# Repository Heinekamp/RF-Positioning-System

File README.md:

# RF-Positioning-System

A cost-effective 2-axis RF positioning system for characterizing antenna directionality in azimuth and elevation, developed as a bachelor project at the EMES chair at the University of Freiburg. Both axes rotate independently around a fixed centre of rotation, controlled by an ESP32 over a standard [SCPI](https://en.wikipedia.org/wiki/Standard_Commands_for_Programmable_Instruments) interface over Ethernet or USB.

## Key Specifications

| Parameter | Value |
|---|---|
| Positioning range | 360° independent rotation, azimuth and elevation |
| Positioning accuracy | 1.0° |
| Positioning speed | 0.1°/s – 180°/s |
| Frequency range | 600 MHz – 6 GHz |
| Payload | 500 g |
| DUT height above base | 1.0 m |
| Base footprint | 40 cm × 40 cm |
| Total weight | ~20 kg |
| Communication | USB, Ethernet (SCPI) |
| Power supply | 12 V DC |

## Measured Performance

Repeatability of both rotation axes, measured with a motion-capture system across 10 repeated full revolutions:

<table>
<tr>
<td width="50%"></td>
<td width="50%"></td>
</tr>
<tr>
<td><sub>Azimuth positioning deviation from the commanded angle, measured after each of 10 repeated full revolutions.</sub></td>
<td><sub>Elevation positioning deviation from the commanded angle, measured the same way.</sub></td>
</tr>
</table>

Radiated emissions of the fully assembled, enclosed system were measured with the Ethernet link forced to 10&nbsp;Mbit/s, against 20 dB under the CISPR 11 Class B radiated emissions limit:

<table>
<tr>
<td width="50%"></td>
<td width="50%"></td>
</tr>
<tr>
<td><sub>Radiated field strength from 0.5–4.5 GHz, vertical and horizontal antenna polarization, against the CISPR 11 Class B limit.</sub></td>
<td><sub>Detail view of the 0.6–1.0 GHz band from the same measurement — individual emission peaks all remain more than 20 dB below the compliance limit shown at left.</sub></td>
</tr>
</table>

## Hardware

The controller is a custom PCB (KiCad project in [`Electrical/Controller`](Electrical/Controller)) built around an ESP32, driving two TMC2209 stepper drivers over UART. The mechanical design was done in Autodesk Fusion 360; the full CAD model is available in the [Fusion 360 online viewer](https://a360.co/42XAUax).

## Software

The firmware is written in C++ using the Arduino framework in PlatformIO (see [`Code/RF-Positioning-System`](Code/RF-Positioning-System)), and exposes a standards-compliant SCPI command set over Ethernet and USB — see that folder's [readme](Code/RF-Positioning-System/readme.md) for the full command reference and a quick-start example.

Firmware documentation is generated with Doxygen and published [here](https://heinekamp.github.io/RF-Positioning-System/index.html). If the following badge is green, it's up to date: .

## Documentation

The [Service Manual](Documentation/manual/ServiceManual.pdf) covers the system's theory of operation, the full SCPI interface, and maintenance/component-replacement procedures.

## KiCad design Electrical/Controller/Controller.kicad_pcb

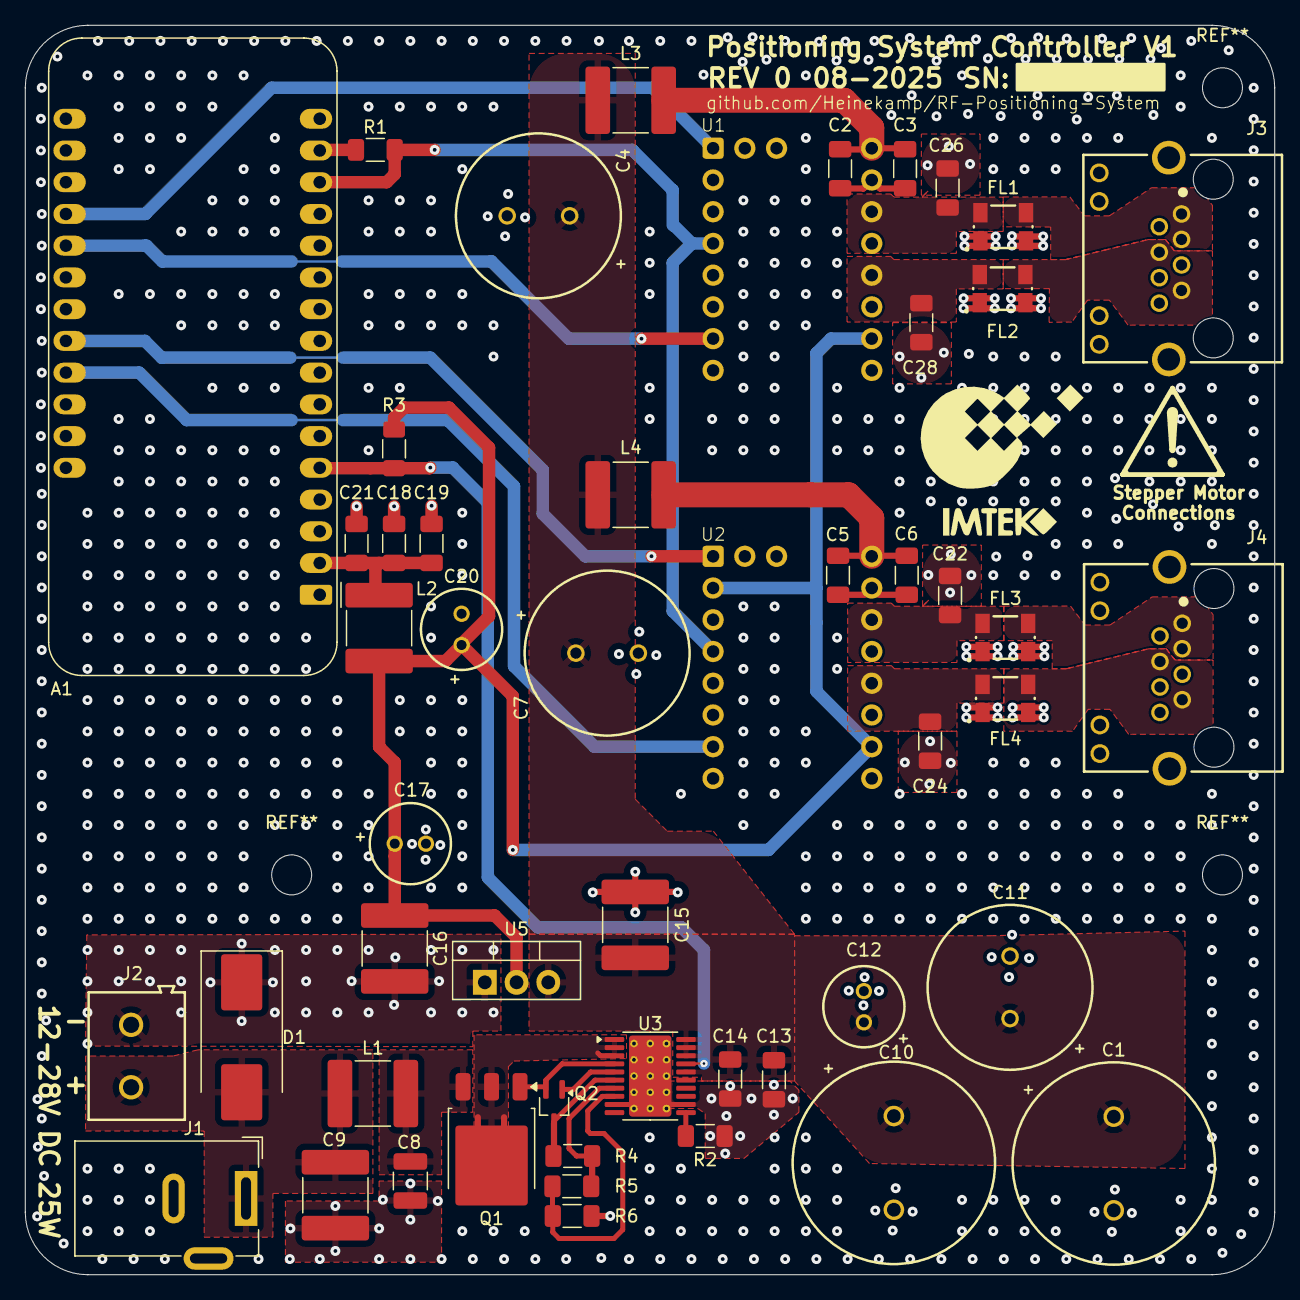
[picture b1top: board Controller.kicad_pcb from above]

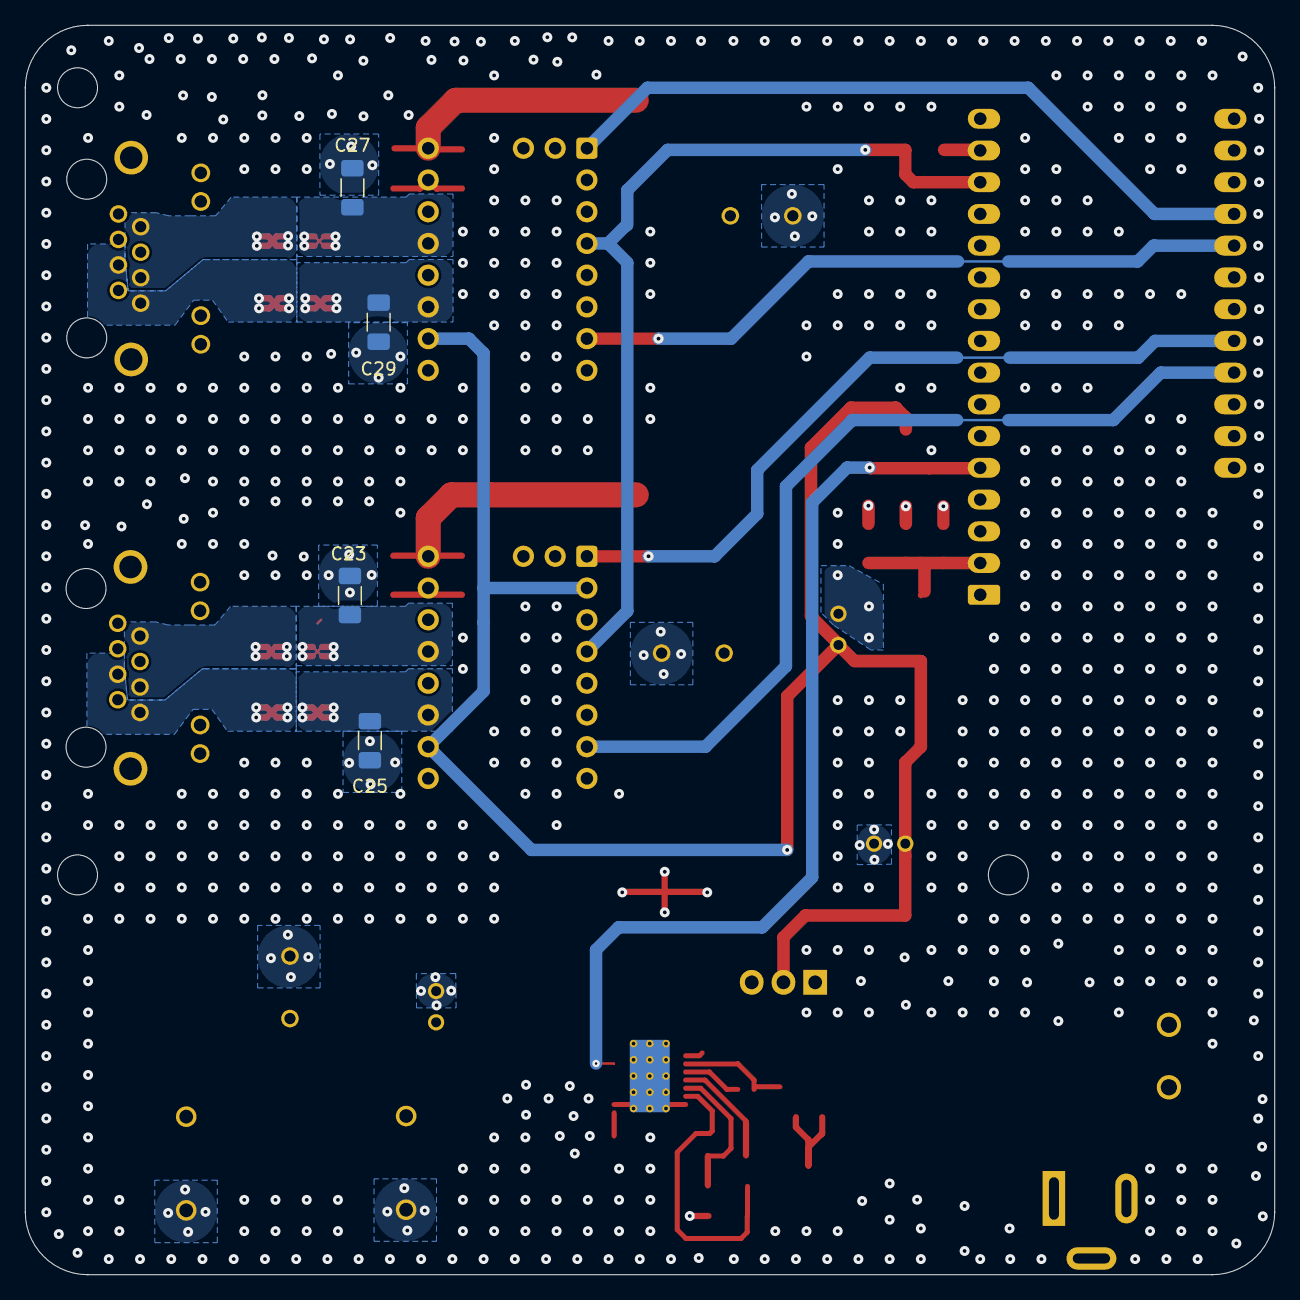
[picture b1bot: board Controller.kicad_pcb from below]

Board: 4 copper layers, 100.0 x 100.0 mm, 55 parts (4 on the bottom side), 38 nets.

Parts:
A1: ESP32; Adafruit_Feather_ESP32
C1, C10: 2200uF; WCAP-ATG8_16X25_DXL_
C2, C3, C5, C6, C13, C19: 100nF; C_1206_3216Metric_Pad1.33x1.80mm_HandSolder
C4, C7, C11: 1000uF; WCAP-ATUL_13X25_DXL_
C8: 1uF; C_1210_3225Metric_Pad1.33x2.70mm_HandSolder
C9, C15, C16: 10uF; C_2220_5750Metric_Pad1.97x5.40mm_HandSolder
C12, C17, C20: 100uF; WCAP-ATG8_6.3X11_DXL_
C14, C18: 10nF; C_1206_3216Metric_Pad1.33x1.80mm_HandSolder
C21: 1nF; C_1206_3216Metric_Pad1.33x1.80mm_HandSolder
C22, C23, C24, C25, C26, C27, C28, C29: 2n2F; C_1206_3216Metric_Pad1.33x1.80mm_HandSolder
D1: SMCJ36CA; D_SMC_Handsoldering
FL1, FL2, FL3, FL4: 744235900; WE-CNSW_1812
J1: 12-28V IN; BarrelJack_Wuerth_6941xx301002
J2: Screw_Terminal_01x02; 691502710002
J3, J4: RJ45_LED_Shielded; Wuerth 615008137421
L1, L2, L3, L4: 600Ω@100 MHz; C_2220_5750Metric_Pad1.97x5.40mm_HandSolder
Q1: DMT10H015LK3-13; TO-252-3_TabPin2
Q2: DMN53D0LW-7; SOT-323_SC-70_Handsoldering
R1: 1k; R_1206_3216Metric_Pad1.30x1.75mm_HandSolder
R2: 6.04k; R_1206_3216Metric_Pad1.30x1.75mm_HandSolder
R3: 10k; R_1206_3216Metric_Pad1.30x1.75mm_HandSolder
R4: 604k; R_1206_3216Metric_Pad1.30x1.75mm_HandSolder
R5: 76.8k; R_1206_3216Metric_Pad1.30x1.75mm_HandSolder
R6: 20k; R_1206_3216Metric_Pad1.30x1.75mm_HandSolder
U1, U2: TMC2209; BTT-TMC2209-V1.3
U3: TPS26631PWP; HTSSOP-20-1EP_4.4x6.5mm_P0.65mm_EP3.4x6.5mm_Mask2.75x3.43mm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
U5: LD1086D2M33TR; TO-220-3_Vertical-v8508a

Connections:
+3V3: C16.1, C17.1, C20.1, L2.1, R3.1, U1.15 (VIO), U2.2 (MS1), U2.15 (VIO), U5.2 (OUT)
/PGOOD: A1.5 (DAC2/A0), R3.2, U3.17 (PGOOD)
/U1.A1: C27.1, FL1.1, U1.12 (A1)
/U1.A2: C26.1, FL1.4, U1.11 (A2)
/U1.B1: C28.1, FL2.4, U1.13 (B1)
/U1.B2: C29.1, FL2.1, U1.14 (B2)
GND: A1.4 (GND), A1.27 (EN), C1.2, C2.2, C3.2, C4.2, C5.2, C6.2, C7.2, C8.2, C9.2, C10.2, C11.2, C12.2, C13.2, C14.2, C15.2, C16.2, C17.2, C18.2, C19.2, C20.2, C21.2, C22.2, C23.2, C24.2, C25.2, C26.2, C27.2, C28.2, C29.2, D1.1 (A1), J1.2, J2.1, R2.2, R6.2, U1.2 (MS2), U1.6 (CLK), U1.10 (GND), U1.16 (GND), U2.6 (CLK), U2.10 (GND), U2.16 (GND), U3.9 (GND), U3.12 (MODE), U3.21 (GND), U5.1 (ADJ/GND)
unnamed: A1.2 (3V3), C18.1, C19.1, C21.1, L2.2
unnamed: A1.20 (A7/IO32), U1.1 (EN)
unnamed: A1.21 (A8/IO15), U1.7 (STEP)
unnamed: A1.24 (A11/IO12), U2.1 (EN)
unnamed: A1.25 (A12/IO13), U2.7 (STEP)
unnamed: A1.14 (RX/IO16), R1.2, U1.4 (RX), U2.4 (RX)
unnamed: A1.15 (TX/IO17), R1.1
unnamed: C8.1, L1.2, Q1.3 (S)
unnamed: C9.1, D1.2 (A2), J1.1, J2.2, L1.1
unnamed: FL1.2, J3.2, J3.6
unnamed: FL1.3, J3.1, J3.3
unnamed: FL2.2, J3.5, J3.8
unnamed: FL2.3, J3.4, J3.7
unnamed: FL3.2, J4.2, J4.6
unnamed: FL3.3, J4.1, J4.3
unnamed: FL4.2, J4.5, J4.8
unnamed: FL4.3, J4.4, J4.7
unnamed: Q1.2 (D), U3.1 (IN), U3.2 (IN), U3.3 (IN)
unnamed: Q1.1 (G), Q2.2 (S), U3.4 (B_GATE)
unnamed: Q2.3 (D), R4.1, U3.6 (IN_SYS)
unnamed: Q2.1 (G), U3.5 (DRV)
unnamed: C2.1, C3.1, L3.1, U1.9 (VM)
unnamed: C23.1, FL3.1, U2.12 (A1)
unnamed: C22.1, FL3.4, U2.11 (A2)
unnamed: C24.1, FL4.4, U2.13 (B1)
unnamed: C25.1, FL4.1, U2.14 (B2)
unnamed: C5.1, C6.1, L4.1, U2.9 (VM)
unnamed: R2.1, U3.11 (ILIM)
unnamed: R5.2, R6.1, U3.8 (OVP)
unnamed: R4.2, R5.1, U3.7 (UVLO)
VIN: C1.1, C4.1, C7.1, C10.1, C11.1, C12.1, C13.1, C14.1, C15.1, L3.2, L4.2, U3.16 (PGTH), U3.18 (OUT), U3.19 (OUT), U3.20 (OUT), U5.3 (IN)
